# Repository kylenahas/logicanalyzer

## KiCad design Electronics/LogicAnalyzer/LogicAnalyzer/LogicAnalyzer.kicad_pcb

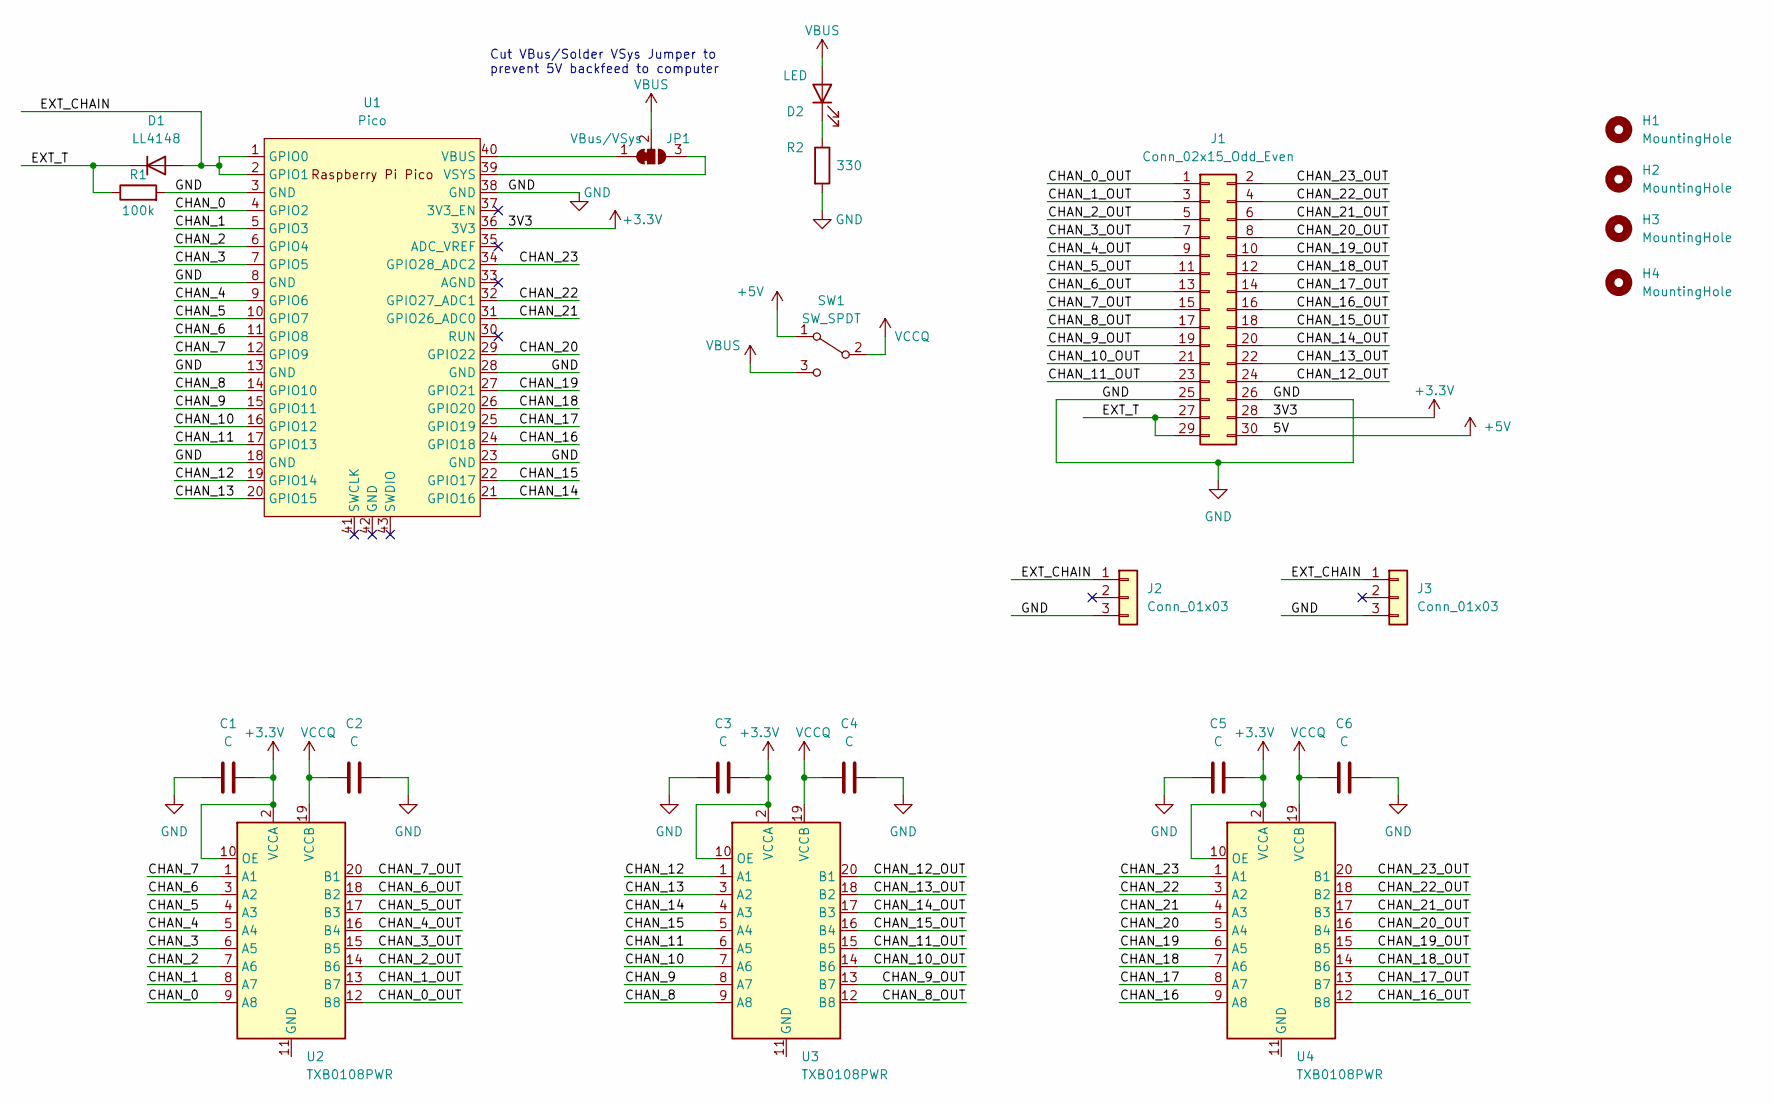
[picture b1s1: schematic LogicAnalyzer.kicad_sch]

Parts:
C1, C2, C3, C4, C5, C6: C; C_0805_2012Metric
D1: LL4148; D_SMA
D2: LED; LED_1206_3216Metric
H1, H2, H3, H4: MountingHole; MountingHole_3.2mm_M3_DIN965_Pad_TopBottom
J1: Conn_02x15_Odd_Even; PinSocket_2x15_P2.54mm_Horizontal
J2: Conn_01x03; PinSocket_1x03_P2.54mm_Horizontal
J3: Conn_01x03; PinHeader_1x03_P2.54mm_Horizontal
JP1: VBus/VSys; SolderJumper-3_P1.3mm_Bridged12_RoundedPad1.0x1.5mm
R1: 100k; R_0805_2012Metric
R2: 330; R_0805_2012Metric
SW1: SW_SPDT; SW_SPDT_PCM12
U1: Pico; RPi_Pico_SMD_TH
U2, U3, U4: TXB0108PWR; TSSOP-20_4.4x6.5mm_P0.65mm

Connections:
+3.3V: C1.2, C3.2, C5.2, J1.28, U1.36 (3V3), U2.2 (VCCA), U2.10 (OE), U3.2 (VCCA), U3.10 (OE), U4.2 (VCCA), U4.10 (OE)
+5V: J1.30, SW1.1 (A)
/CHAN_0: U1.4 (GPIO2), U2.9 (A8)
/CHAN_0_OUT: J1.1, U2.12 (B8)
/CHAN_1: U1.5 (GPIO3), U2.8 (A7)
/CHAN_1_OUT: J1.3, U2.13 (B7)
/CHAN_2: U1.6 (GPIO4), U2.7 (A6)
/CHAN_2_OUT: J1.5, U2.14 (B6)
/CHAN_3: U1.7 (GPIO5), U2.6 (A5)
/CHAN_3_OUT: J1.7, U2.15 (B5)
/CHAN_4: U1.9 (GPIO6), U2.5 (A4)
/CHAN_4_OUT: J1.9, U2.16 (B4)
/CHAN_5: U1.10 (GPIO7), U2.4 (A3)
/CHAN_5_OUT: J1.11, U2.17 (B3)
/CHAN_6: U1.11 (GPIO8), U2.3 (A2)
/CHAN_6_OUT: J1.13, U2.18 (B2)
/CHAN_7: U1.12 (GPIO9), U2.1 (A1)
/CHAN_7_OUT: J1.15, U2.20 (B1)
/CHAN_8: U1.14 (GPIO10), U3.9 (A8)
/CHAN_8_OUT: J1.17, U3.12 (B8)
/CHAN_9: U1.15 (GPIO11), U3.8 (A7)
/CHAN_9_OUT: J1.19, U3.13 (B7)
/CHAN_10: U1.16 (GPIO12), U3.7 (A6)
/CHAN_10_OUT: J1.21, U3.14 (B6)
/CHAN_11: U1.17 (GPIO13), U3.6 (A5)
/CHAN_11_OUT: J1.23, U3.15 (B5)
/CHAN_12: U1.19 (GPIO14), U3.1 (A1)
/CHAN_12_OUT: J1.24, U3.20 (B1)
/CHAN_13: U1.20 (GPIO15), U3.3 (A2)
/CHAN_13_OUT: J1.22, U3.18 (B2)
/CHAN_14: U1.21 (GPIO16), U3.4 (A3)
/CHAN_14_OUT: J1.20, U3.17 (B3)
/CHAN_15: U1.22 (GPIO17), U3.5 (A4)
/CHAN_15_OUT: J1.18, U3.16 (B4)
/CHAN_16: U1.24 (GPIO18), U4.9 (A8)
/CHAN_16_OUT: J1.16, U4.12 (B8)
/CHAN_17: U1.25 (GPIO19), U4.8 (A7)
/CHAN_17_OUT: J1.14, U4.13 (B7)
/CHAN_18: U1.26 (GPIO20), U4.7 (A6)
/CHAN_18_OUT: J1.12, U4.14 (B6)
/CHAN_19: U1.27 (GPIO21), U4.6 (A5)
/CHAN_19_OUT: J1.10, U4.15 (B5)
/CHAN_20: U1.29 (GPIO22), U4.5 (A4)
/CHAN_20_OUT: J1.8, U4.16 (B4)
/CHAN_21: U1.31 (GPIO26_ADC0), U4.4 (A3)
/CHAN_21_OUT: J1.6, U4.17 (B3)
/CHAN_22: U1.32 (GPIO27_ADC1), U4.3 (A2)
/CHAN_22_OUT: J1.4, U4.18 (B2)
/CHAN_23: U1.34 (GPIO28_ADC2), U4.1 (A1)
/CHAN_23_OUT: J1.2, U4.20 (B1)
/EXT_CHAIN: D1.2 (A), J2.1, J3.1, U1.1 (GPIO0), U1.2 (GPIO1)
/EXT_T: D1.1 (K), J1.27, J1.29, R1.1
GND: C1.1, C2.2, C3.1, C4.2, C5.1, C6.2, H1.1, H2.1, H3.1, H4.1, J1.25, J1.26, J2.3, J3.3, R1.2, R2.2, U1.3 (GND), U1.8 (GND), U1.13 (GND), U1.18 (GND), U1.23 (GND), U1.28 (GND), U1.38 (GND)
unnamed: D2.1 (K), R2.1
unnamed: JP1.1 (A), U1.40 (VBUS)
unnamed: JP1.3 (B), U1.39 (VSYS)
VBUS: D2.2 (A), JP1.2 (C), SW1.3 (C)
VCCQ: C2.1, C4.1, C6.1, SW1.2 (B), U2.19 (VCCB), U3.19 (VCCB), U4.19 (VCCB)

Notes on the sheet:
Cut VBus/Solder VSys Jumper to prevent 5V backfeed to computer

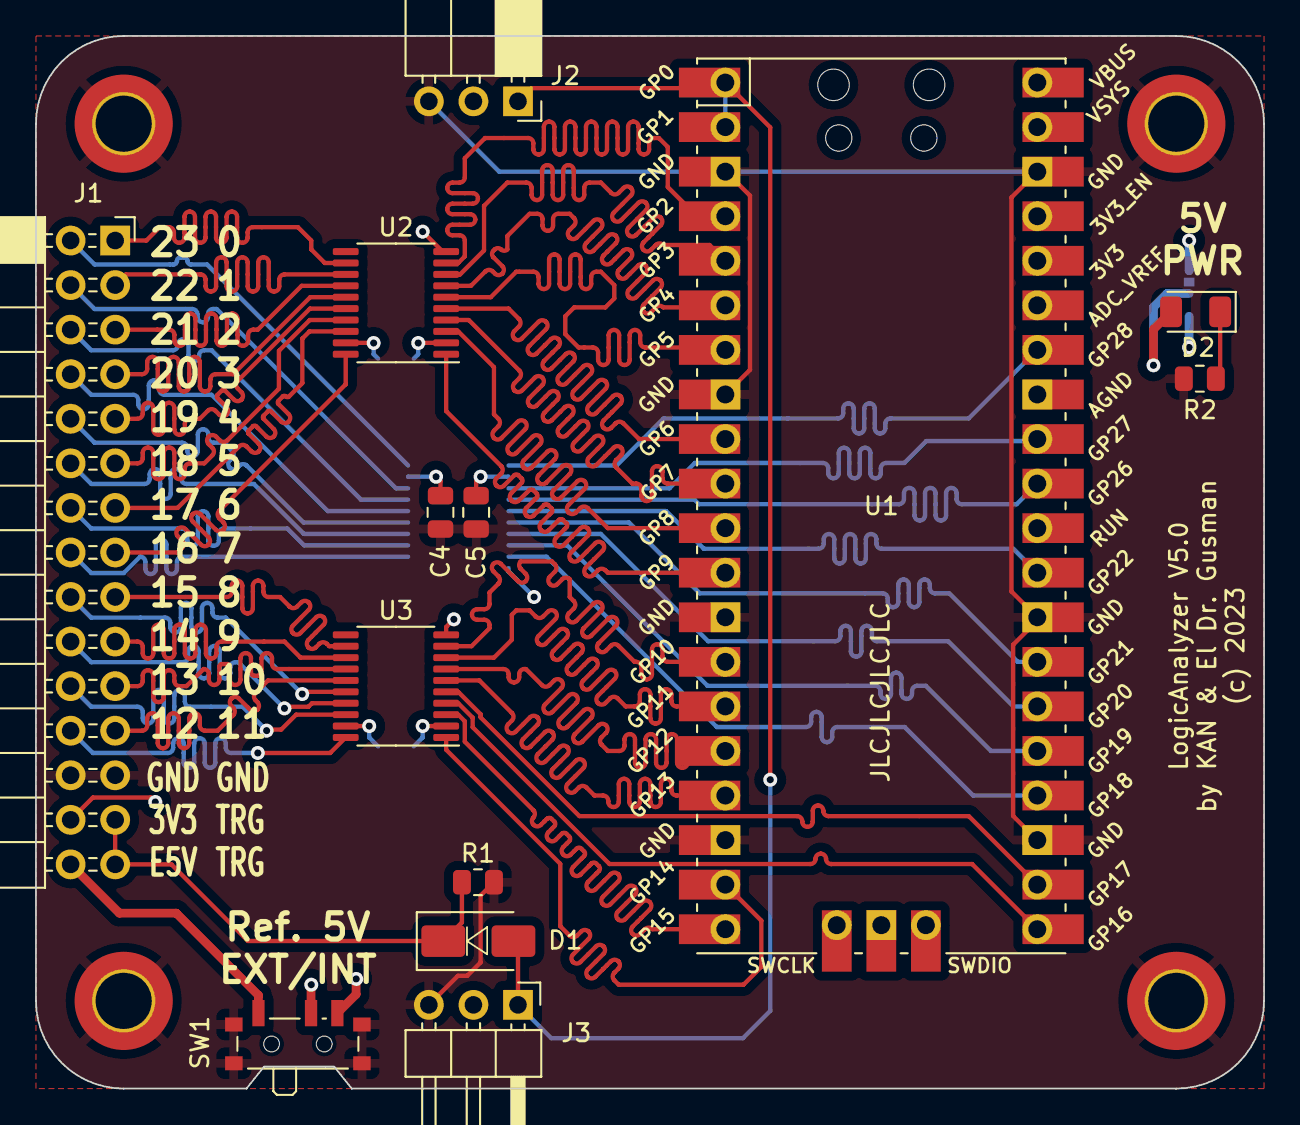
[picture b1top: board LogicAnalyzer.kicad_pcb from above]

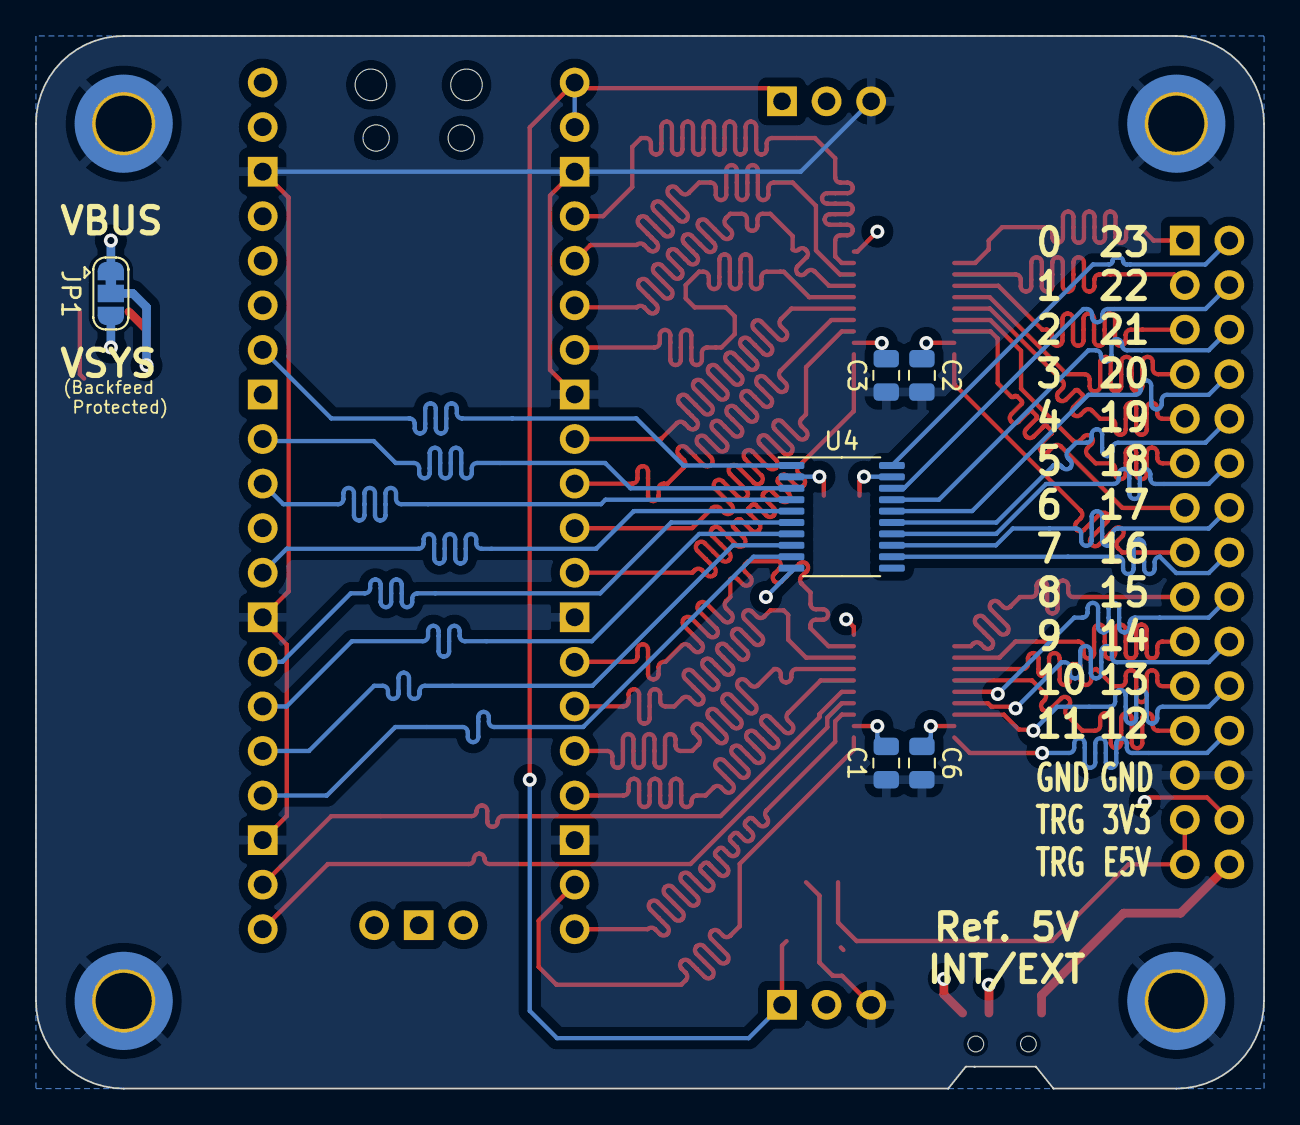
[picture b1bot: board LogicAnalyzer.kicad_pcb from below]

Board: 4 copper layers, 70.0 x 60.0 mm, 23 parts (6 on the bottom side), 58 nets.

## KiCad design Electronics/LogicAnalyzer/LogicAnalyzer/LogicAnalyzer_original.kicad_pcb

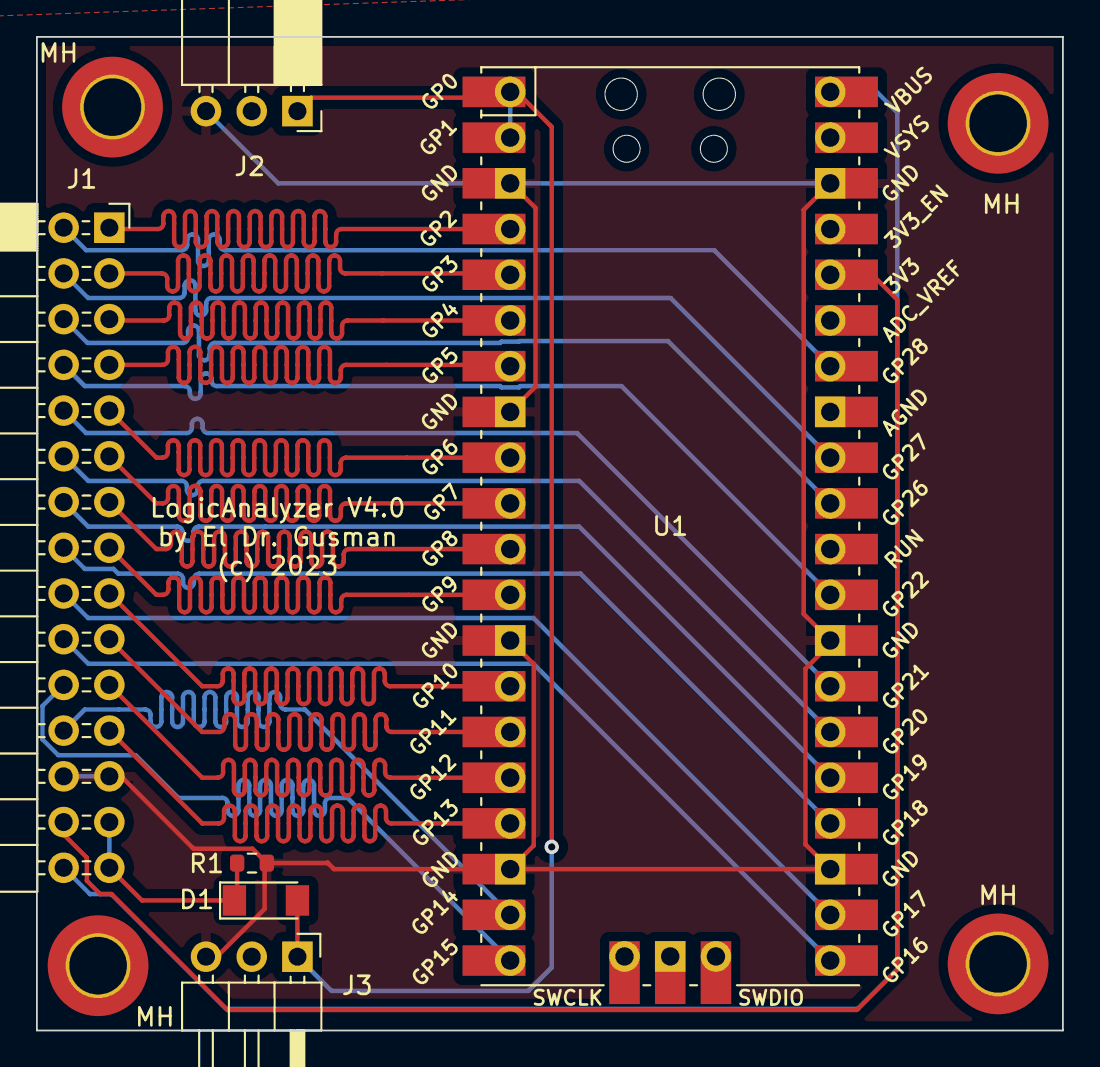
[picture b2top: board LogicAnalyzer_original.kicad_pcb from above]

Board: 2 copper layers, 57.0 x 55.2 mm, 10 parts (0 on the bottom side), 29 nets.

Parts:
D1: LL4148; D_MiniMELF
J1: Conn_02x15_Odd_Even; PinSocket_2x15_P2.54mm_Horizontal
J2: Conn_01x03; PinSocket_1x03_P2.54mm_Horizontal
J3: Conn_01x03; PinHeader_1x03_P2.54mm_Horizontal
MH: MountingHole_3.2mm_M3_DIN965_Pad_TopBottom
MH#2, MH#3, MH#4: MountingHole_3.2mm_M3_DIN965_Pad_TopBottom
R1: 100k; R_0603_1608Metric
U1: Pico; RPi_Pico_SMD_TH

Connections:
/3V3: J1.28, U1.36 (3V3)
/5V: J1.30, U1.40 (VBUS)
/CHAN_0: J1.1, U1.4 (GPIO2)
/CHAN_1: J1.3, U1.5 (GPIO3)
/CHAN_2: J1.5, U1.6 (GPIO4)
/CHAN_3: J1.7, U1.7 (GPIO5)
/CHAN_4: J1.9, U1.9 (GPIO6)
/CHAN_5: J1.11, U1.10 (GPIO7)
/CHAN_6: J1.13, U1.11 (GPIO8)
/CHAN_7: J1.15, U1.12 (GPIO9)
/CHAN_8: J1.17, U1.14 (GPIO10)
/CHAN_9: J1.19, U1.15 (GPIO11)
/CHAN_10: J1.21, U1.16 (GPIO12)
/CHAN_11: J1.23, U1.17 (GPIO13)
/CHAN_12: J1.24, U1.19 (GPIO14)
/CHAN_13: J1.22, U1.20 (GPIO15)
/CHAN_14: J1.20, U1.21 (GPIO16)
/CHAN_15: J1.18, U1.22 (GPIO17)
/CHAN_16: J1.16, U1.24 (GPIO18)
/CHAN_17: J1.14, U1.25 (GPIO19)
/CHAN_18: J1.12, U1.26 (GPIO20)
/CHAN_19: J1.10, U1.27 (GPIO21)
/CHAN_20: J1.8, U1.29 (GPIO22)
/CHAN_21: J1.6, U1.31 (GPIO26_ADC0)
/CHAN_22: J1.4, U1.32 (GPIO27_ADC1)
/CHAN_23: J1.2, U1.34 (GPIO28_ADC2)
/EXT_CHAIN: D1.2 (A), J2.1, J3.1, U1.1 (GPIO0), U1.2 (GPIO1)
/EXT_T: D1.1 (K), J1.27, J1.29, R1.1
/GND: J1.25, J1.26, J2.3, J3.3, R1.2, U1.3 (GND), U1.8 (GND), U1.13 (GND), U1.18 (GND), U1.23 (GND), U1.28 (GND), U1.38 (GND)

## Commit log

2023-10-09 Version 5.0 of PCB
    - Integrated bidirectional voltage translators
    - Added Power LED
    - Switchable internal or external reference voltage

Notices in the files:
Electronics/LogicAnalyzer/LogicAnalyzer/LogicAnalyzer.kicad_pcb:
(c) 2023
